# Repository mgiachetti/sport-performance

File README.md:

# Sport Performance

Plataforma de rendimiento para deportes juveniles (M13 a M19), white-label multi-tenant. Contexto de producto y dominio en [`CLAUDE.md`](CLAUDE.md); backlog en [`docs/backlog.md`](docs/backlog.md); decisiones en [`docs/adr/`](docs/adr/).

## Requisitos

- Node 24 (`.nvmrc`)
- pnpm (versión fijada en `packageManager`; con Corepack: `corepack enable`)
- Docker, para Postgres local en los tests de integración

## Comandos

| Comando | Qué hace |
|---|---|
| `pnpm install` | Instala dependencias de todo el workspace |
| `pnpm build` | Compila los paquetes y servicios (`dist/`) en orden de dependencias |
| `pnpm lint` | ESLint con reglas *type-checked*, sin warnings permitidos |
| `pnpm typecheck` | `tsc --noEmit` en cada paquete |
| `pnpm test` | Vitest en cada paquete |
| `pnpm format` / `pnpm format:check` | Prettier en todo el repo |
| `pnpm dev` | Modo watch de cada paquete |
| `pnpm docs:check` | Valida los ADRs de `docs/adr/`, su índice y los enlaces desde `CLAUDE.md` |

Todas las tareas pasan por Turborepo y se cachean. Para correr una tarea en un solo paquete: `pnpm turbo run test --filter=@sport-performance/domain`.

## CI

GitHub Actions (`.github/workflows/ci.yml`) corre en cada PR y en cada push a `main`, con jobs en paralelo: `format`, `lint`, `typecheck`, `test`, `build` y `workflows` (actionlint y shellcheck). El job `test` tiene un Postgres 16 de servicio y expone `DATABASE_URL` para los tests de integración; localmente se levanta con Docker (`postgres:16`) y se exporta la misma variable.

El job **`ci`** agrega a todos los demás y es el único check requerido en `main`: si agregás un job, sumalo a `needs` de `ci` (el job `workflows` falla si falta). Las acciones de terceros se fijan por SHA de commit.

## Estructura

```
apps/
  api/        API HTTP (Fastify + zod, Better Auth, RLS)
  worker/     Jobs en segundo plano (pg-boss)
  web/        Web del staff (React + Vite + TanStack)
  mobile/     App de jugadores y staff (Expo)
packages/
  domain/     Modelo y fórmulas puras del dominio
  contracts/  Esquemas zod, OpenAPI y cliente tipado
  ui-tokens/  Tokens de diseño y tema por club
  i18n/       Mensajes ICU y formatos es-AR
  config/     tsconfig, ESLint y Vitest compartidos
mockups/      Maqueta de referencia (no es diseño final)
assets/       Marcas por club (assets/clubs/<club>/)
firmware/     Firmware del pod (Fase 3)
docs/         Backlog y ADRs
```

Las apps son por ahora esqueletos: cada framework entra con su propio issue del backlog.

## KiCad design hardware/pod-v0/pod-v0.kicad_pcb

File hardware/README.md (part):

# Hardware

Proyectos de KiCad del pod GNSS + IMU (Fase 3). El diseño está en [`docs/hardware/pod-v0.md`](../docs/hardware/pod-v0.md) y las decisiones en el [ADR 0105](../docs/adr/0105-pod-gnss-imu-con-telemetria-en-vivo.md).

| Carpeta | Qué hay |
|---|---|
| `pod-v0/` | Proyecto de la v0 (B-909): esquemático jerárquico, placa de 6 capas con su apilado, clases de red (`pod-v0.kicad_pro`), reglas de diseño (`pod-v0.kicad_dru`); las salidas de fabricación salen de `tools/fabricacion.py` |
| `lib/` | Librería propia: símbolos, footprints y modelos 3D de los módulos (ver [`lib/README.md`](lib/README.md)) |

## Versión de KiCad

- Los archivos se crearon en el formato de KiCad 8, que abren KiCad 8, 9 y 10. Al guardarlos con una versión más nueva, se actualizan a su formato: a partir de ahí hay que usar esa versión o una posterior. **La placa (`pod-v0.kicad_pcb`) ya está en el formato de KiCad 10** desde el 14/11/2026 (contorno, tornillos y zonas guardados con el pcbnew 10.0.8 de la imagen del CI): se abre con KiCad 10 o posterior. El esquemático sigue en el de KiCad 8.
- El CI usa la imagen oficial `kicad/kicad:10.0.8`, fijada por digest en `.github/workflows/hardware.yml`. Lee los archivos de cualquiera de esas versiones.

## Cómo se trabaja

- **Ubicación y ruteo, a mano en KiCad** desde el arranque de `ubicar.py` y `rutear.py` (15/11/2026), en especial la RF: línea de 50 Ω, plano de tierra del patch GNSS (la antena principal: patch pasivo apilado L1 + L5 en la placa, con SAW y LNA montados; la Taoglas activa va por U.FL como rescate), separación de LoRa.
- **Claude Code** se encarga de:
  - generar y revisar los símbolos y footprints de los módulos a partir de las hojas;
  - correr ERC y DRC;
  - preparar las salidas de fabricación;
  - revisar cada cambio del esquemático o de la placa en el PR, contra `docs/hardware/pod-v0.md`.
- **El esquemático se genera** desde una netlist declarativa (ver abajo): siete hojas jerárquicas (`power`, `gnss_rf`, `mcu_radio`, `sensors`, `storage`, `usb_dock`, `uwb`) con todas las partes de `docs/hardware/pod-v0.md`, incluidos los lugares de rescate (marcados con el DNP nativo de KiCad). **La placa tiene todas las partes ubicadas y desde el 23/11/2026 es de 6 capas, ruteada entera por script desde el 26/11/2026** (ver "Ubicación inicial" y "Ruteo"), además del apilado de 6 capas, el contorno de 50 × 70 mm, las reglas de diseño y las zonas de las antenas (ver "Reglas de diseño de la placa").

## Ubicación inicial (`tools/ubicar.py`)

Las partes entraron a la placa el 15/11/2026 con `tools/ubicar.py`, una herramienta **de una sola vez** (bootstrap): desde ahí **la ubicación y el ruteo siguen a mano en KiCad** y la fuente es la placa, no la tabla. Corre dentro de la imagen de KiCad del CI (usa el módulo `pcbnew` y `kicad-cli`):

```sh
docker run --rm -e HOME=/tmp -v "$PWD:/work" -w /work kicad/kicad:10.0.8@sha256:3f4a… python3 hardware/tools/ubicar.py
```

1. Exporta la netlist del esquemático con `kicad-cli sch export netlist` (lo mismo que lee "Tools → Update PCB from Schematic").
2. Agrega cada footprint que falta con lo que escribe la actualización desde el esquemático: referencia, valor, los campos del símbolo (MPN, LCSC, Fabricante, Verificado, Nota), el camino de la hoja (así una actualización posterior desde KiCad y `--schematic-parity` los reconocen), DNP, si va a la BOM y la red de cada pad. Los pines sin conectar quedan en redes `unconnected-(…)`, como las crea KiCad.
3. Ubica cada parte según [`tools/datos/ubicacion_pod_v0.csv`](tools/datos/ubicacion_pod_v0.csv) (`ref`, `x`, `y` en mm del documento, origen (0; 0) = (100; 100) en KiCad; `rot` como la muestra KiCad; `cara` F o B; `fijo` = bloqueado; `nota`), pone las referencias en 0,8 mm en un lugar libre al lado de cada parte (o las oculta en la serigrafía si no hay; siguen en F.Fab/B.Fab), rellena las zonas y guarda. No rutea nada. No toca `pod-v0.kicad_pro` (guardar desde Python lo reescribe entero).

Por defecto **solo agrega y ubica las partes que faltan** (por ejemplo, después de sumar una parte en `diseno.py`) y no mueve ni retoca las que ya están: sobre la placa del repositorio no cambia nada (verificado: correrla de nuevo deja el archivo igual). `--reubicar-todo` vuelve a poner cada parte en su lugar de la tabla, bloqueadas incluidas, y no corre si la placa ya tiene pistas o vías. Todas las partes del esquemático van en la placa: la tapa blindada `SH201`, la única que había quedado afuera ("excluir de la placa"), salió del diseño el 15/11/2026 (`docs/hardware/pod-v0-ubicacion-y-carcasa.md`, sección 9). La prueba de ruteo que respalda la ubicación está en la misma sección.

## Ruteo (`tools/rutear.py`)

La placa está **ruteada entera** desde el 26/11/2026: 0 conexiones sin rutear, 0 violaciones y 0 diferencias con el esquemático. Desde el 28/11/2026 **no tiene vías en los pads**, así que no necesita relleno de resina (ADR 0105, "Registro de decisiones"). Se ruteó por script en 4 capas el 15 y 16/11/2026, en parte (quedaron 147 conexiones en 55 redes); después de tres corridas de Quilter y del router propio que no la cerraron, desde el 23/11/2026 es de **6 capas** (ADR 0105, "Registro de decisiones"), y la versión del repositorio sale de una corrida completa desde la placa ubicada (detalle en [`pod-v0-ubicacion-y-carcasa.md`](../docs/hardware/pod-v0-ubicacion-y-carcasa.md), sección 9, "Ruteo"). Como `ubicar.py`, es un procedimiento **de una sola vez**: desde ahí la fuente es la placa y los cambios siguen a mano en KiCad (las pistas de `criticas` quedan bloqueadas). **No hay que volver a correrlo sobre la placa del repositorio**: se corre en una copia (`--placa`) y la placa nueva reemplaza a la otra solo si el DRC del CI pasa entero. Cada paso corre en la imagen de KiCad del CI. Lleva unas 14 h en total, casi todo `resto`: sin vías en los pads, cada vuelta tarda unos 6 min.

```sh
K="docker run --rm -e HOME=/tmp -v $PWD:/work -w /work kicad/kicad:10.0.8@sha256:3f4a…"
P="--placa hardware/pod-v0/copia.kicad_pcb"  # una copia de la placa, con su .kicad_pro y .kicad_dru al lado
$K python3 hardware/tools/ubicar.py $P             # redes de cada pad desde el esquemático
$K python3 hardware/tools/rutear.py limpiar $P     # saca pistas, vías y planos de L1, L3, L4 y L6
$K python3 hardware/tools/rutear.py criticas $P --forzar  # pasivas de MOVES y redes críticas, bloqueadas
$K python3 hardware/tools/rutear.py abanico $P     # una vía de GND al lado de cada pad de GND
$K python3 hardware/tools/rutear.py resto $P --vueltas 128  # todo lo demás salvo GND (tools/laberinto.py)
$K python3 hardware/tools/rutear.py reparar $P --margen 0.5  # las redes sin terminar y las de al lado, otra vez
$K python3 hardware/tools/rutear.py planos $P      # relleno de GND en L1, L3, L4 y L6 y costura; rellena
$K python3 hardware/tools/rutear.py remate $P      # lo que haya quedado suelto, por el lugar libre
$K python3 hardware/tools/rutear.py podar $P       # saca lo que el DRC marca y el cobre colgado
$K python3 hardware/tools/rutear.py rescate $P     # vía para los pads de GND encerrados, si queda alguno
$K python3 hardware/tools/rutear.py podar $P
# mientras quede algo sin rutear: retocar con otro radio, y planos, remate, podar, rescate y podar
$K python3 hardware/tools/rutear.py retocar $P --radio 2.25
```

**Cómo salió la placa del repositorio (28/11/2026).** Hizo falta más que la secuencia de arriba:
- `resto` con 128 vueltas llegó a 3 redes en conflicto en la vuelta 118 y volvió a esa vuelta al final.
- `reparar --margen 0.5` dejó una sola conexión sin rutear.
- El escape de `BAT_NTC` y la vía de GND del eFuse de `pads_encerrados` se agregaron sobre esa placa con un script de una sola vez, que tiene las mismas pistas que `criticas`. Cada uno levantó y volvió a rutear las redes con las que chocaba.
- Después hubo dos pasadas de `retocar`: con 2 mm de radio quedaron 2 conexiones, y con 2,25 mm, 0.

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
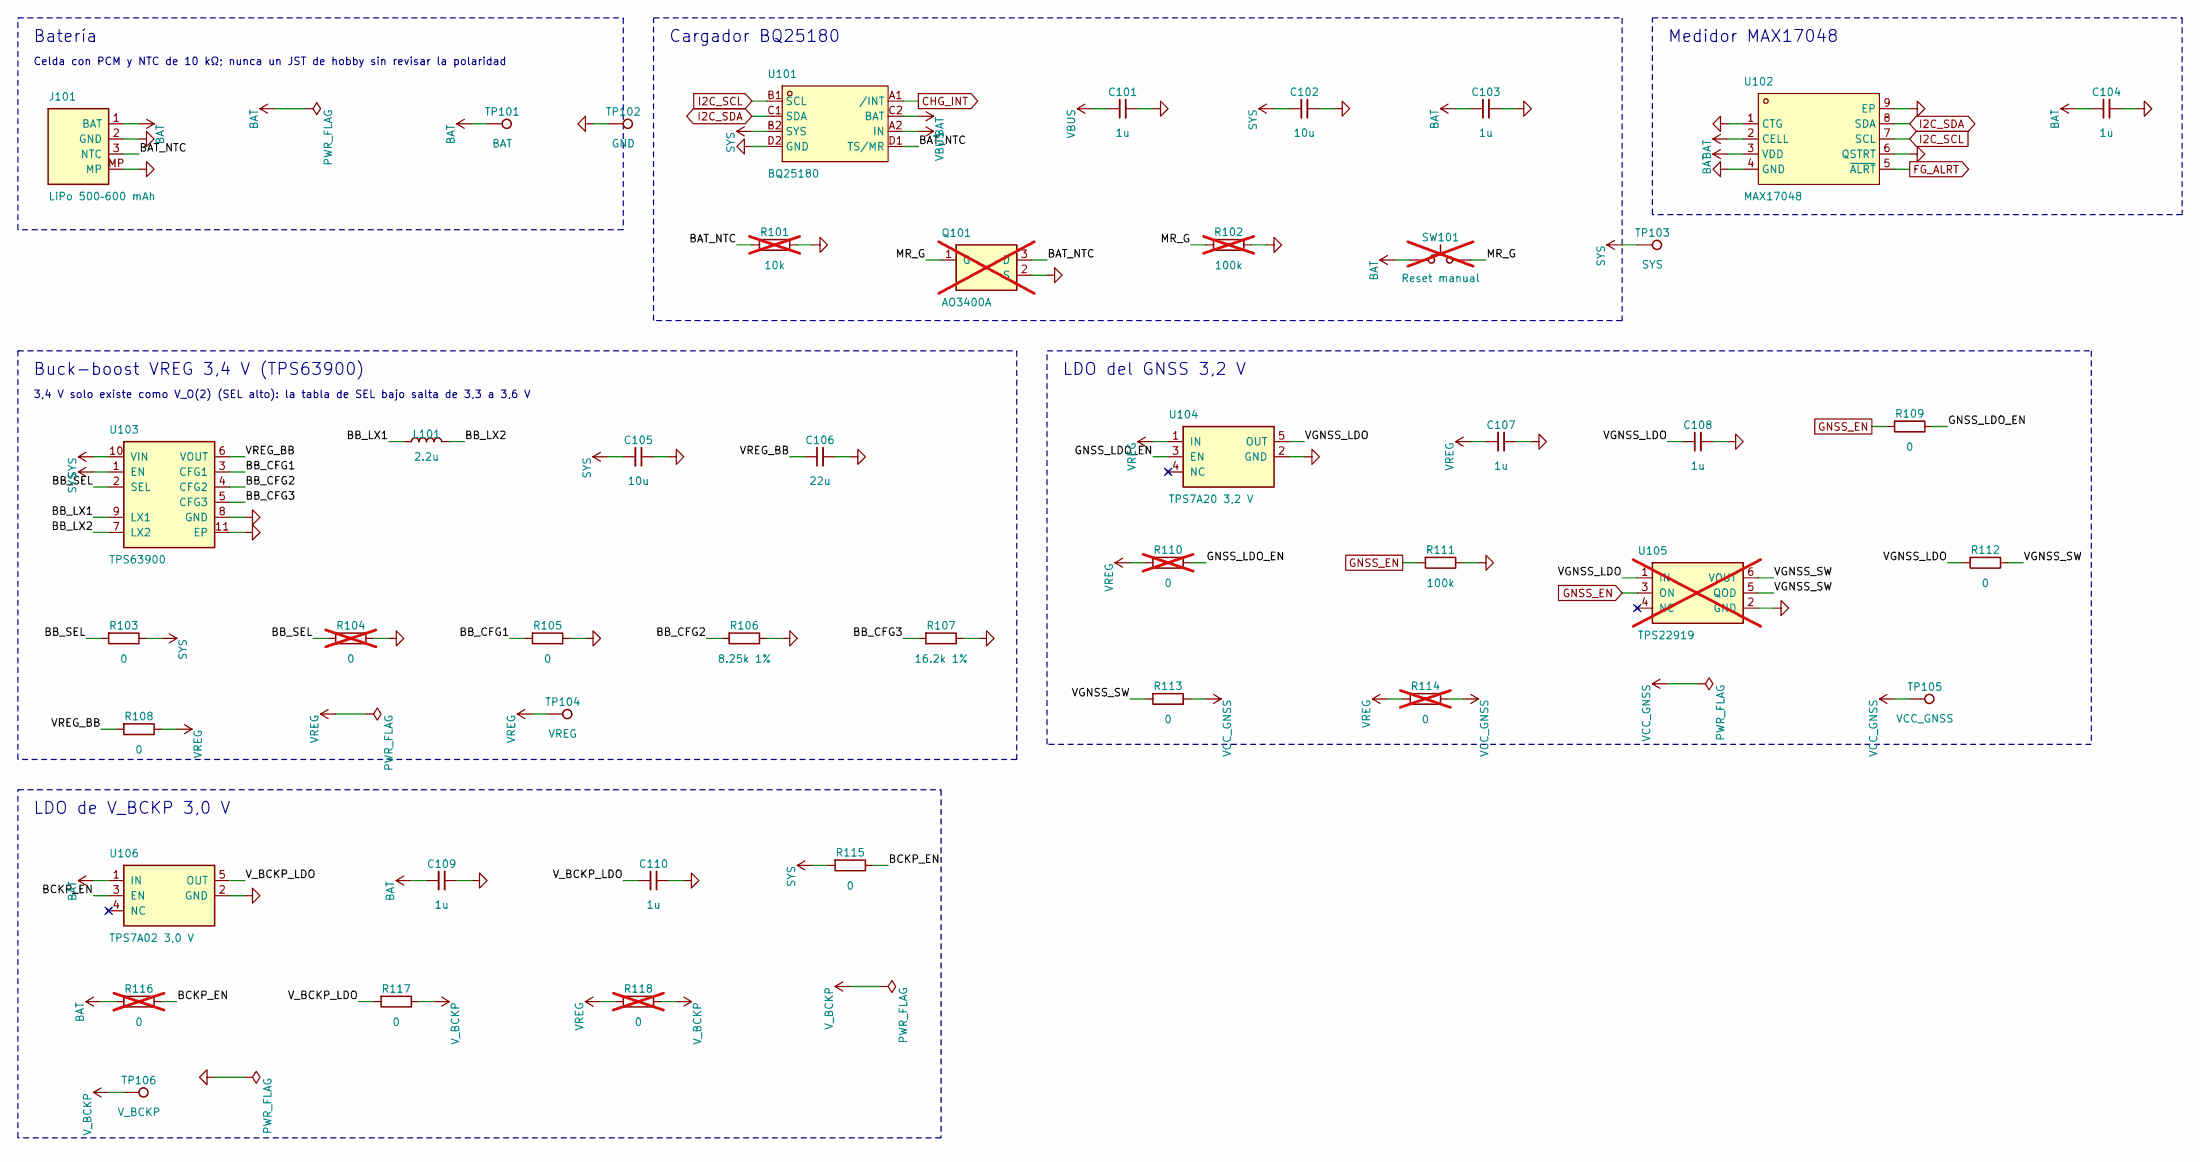
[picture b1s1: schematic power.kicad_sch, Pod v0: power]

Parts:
C101, C103, C104, C107, C108, C109, C110: 1u; C_0402_1005Metric; MPN CL05A105KA5NQNC; LCSC C52923
C102, C105: 10u; C_0603_1608Metric; MPN CL10A106KP8NNNC; LCSC C19702
C106: 22u; C_0603_1608Metric; MPN CL10A226MQ8NRNC; LCSC C59461
J101: LiPo 500–600 mAh; JST_GH_SM03B-GHS-TB_1x03-1MP_P1.25mm_Horizontal; MPN SM03B-GHS-TB(LF)(SN); LCSC C514175
L101: 2.2u; L_Murata_DFE201610P; MPN DFE201612E-2R2M=P2; LCSC C337893
Q101: AO3400A; SOT-23; MPN AO3400A; LCSC C20917; not fitted
R101: 10k; R_0402_1005Metric; MPN 0402WGF1002TCE; LCSC C25744; not fitted
R102: 100k; R_0402_1005Metric; MPN 0402WGF1003TCE; LCSC C25741; not fitted
R103, R105, R108, R109, R112, R113, R115, R117: 0; R_0402_1005Metric; MPN 0402WGF0000TCE; LCSC C17168
R104, R110, R114, R116, R118: 0; R_0402_1005Metric; MPN 0402WGF0000TCE; LCSC C17168; not fitted
R106: 8.25k 1%; R_0402_1005Metric; MPN 0402WGF8251TCE; LCSC C95598
R107: 16.2k 1%; R_0402_1005Metric; MPN 0402WGF1622TCE; LCSC C27176
R111: 100k; R_0402_1005Metric; MPN 0402WGF1003TCE; LCSC C25741
SW101: Reset manual; SW_SPST_TL3342; MPN TL3342F450QG; LCSC C2886897; not fitted
TP101: BAT; TestPoint_Pad_D1.0mm
TP102: GND; TestPoint_Pad_D1.0mm
TP103: SYS; TestPoint_Pad_D1.0mm
TP104: VREG; TestPoint_Pad_D1.0mm
TP105: VCC_GNSS; TestPoint_Pad_D1.0mm
TP106: V_BCKP; TestPoint_Pad_D1.0mm
U101: BQ25180; DSBGA-8_L1.6-W0.9-R2-C4-P0.40-BL; MPN BQ25180YBGR; LCSC C3682423
U102: MAX17048; TDFN-8_L2.0-W2.0-P0.50-BL-EP1.2; MPN MAX17048G+T10; LCSC C2682616
U103: TPS63900; Texas_DSK0010A_WSON-10-1EP_2.5x2.5mm_P0.5mm_EP1.2x2mm_Therm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; MPN TPS63900DSKR; LCSC C1518762
U104: TPS7A20 3,2 V; SOT-23-5; MPN TPS7A2032PDBVR; LCSC C2877862
U105: TPS22919; SOT-363_SC-70-6; MPN TPS22919DCKR; LCSC C2149796; not fitted
U106: TPS7A02 3,0 V; SOT-23-5; MPN TPS7A0230PDBVR; LCSC C3747031

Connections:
/power/BAT_NTC: J101.3 (NTC), Q101.3 (D), R101.1, U101.D1 (TS/MR)
/power/BB_CFG1: R105.1, U103.3 (CFG1)
/power/BB_CFG2: R106.1, U103.4 (CFG2)
/power/BB_CFG3: R107.1, U103.5 (CFG3)
/power/BB_LX1: L101.1, U103.9 (LX1)
/power/BB_LX2: L101.2, U103.7 (LX2)
/power/BB_SEL: R103.1, R104.1, U103.2 (SEL)
/power/BCKP_EN: R115.2, R116.2, U106.3 (EN)
/power/GNSS_LDO_EN: R109.2, R110.2, U104.3 (EN)
/power/MR_G: Q101.1 (G), R102.1, SW101.2
/power/VGNSS_LDO: C108.1, R112.1, U104.5 (OUT), U105.1 (IN)
/power/VGNSS_SW: R112.2, R113.1, U105.5 (QOD), U105.6 (VOUT)
/power/VREG_BB: C106.1, R108.1, U103.6 (VOUT)
/power/V_BCKP_LDO: C110.1, R117.1, U106.5 (OUT)
BAT: C103.1, C104.1, C109.1, J101.1 (BAT), R116.1, SW101.1, TP101.1, U101.C2 (BAT), U102.2 (CELL), U102.3 (VDD), U106.1 (IN)
CHG_INT: U101.A1 (/INT); also elsewhere on the board
FG_ALRT: U102.5 (~ALRT); also elsewhere on the board
GND: C101.2, C102.2, C103.2, C104.2, C105.2, C106.2, C107.2, C108.2, C109.2, C110.2, J101.2 (GND), J101.MP, Q101.2 (S), R101.2, R102.2, R104.2, R105.2, R106.2, R107.2, R111.2, TP102.1, U101.D2 (GND), U102.1 (CTG), U102.4 (GND), U102.6 (QSTRT), U102.9 (EP), U103.8 (GND), U103.11 (EP), U104.2 (GND), U105.2 (GND), U106.2 (GND); also elsewhere on the board
GNSS_EN: R109.1, R111.1, U105.3 (ON); also elsewhere on the board
I2C_SCL: U101.B1 (SCL), U102.7 (SCL); also elsewhere on the board
I2C_SDA: U101.C1 (SDA), U102.8 (SDA); also elsewhere on the board
SYS: C102.1, C105.1, R103.2, R115.1, TP103.1, U101.B2 (SYS), U103.1 (EN), U103.10 (VIN); also elsewhere on the board
VBUS: C101.1, U101.A2 (IN); also elsewhere on the board
VCC_GNSS: R113.2, R114.2, TP105.1; also elsewhere on the board
VREG: C107.1, R108.2, R110.1, R114.1, R118.1, TP104.1, U104.1 (IN); also elsewhere on the board
V_BCKP: R117.2, R118.2, TP106.1; also elsewhere on the board

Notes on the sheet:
Batería
Celda con PCM y NTC de 10 kΩ; nunca un JST de hobby sin revisar la polaridad
Cargador BQ25180
Medidor MAX17048
Buck-boost VREG 3,4 V (TPS63900)
3,4 V solo existe como V_O(2) (SEL alto): la tabla de SEL bajo salta de 3,3 a 3,6 V
LDO del GNSS 3,2 V
LDO de V_BCKP 3,0 V

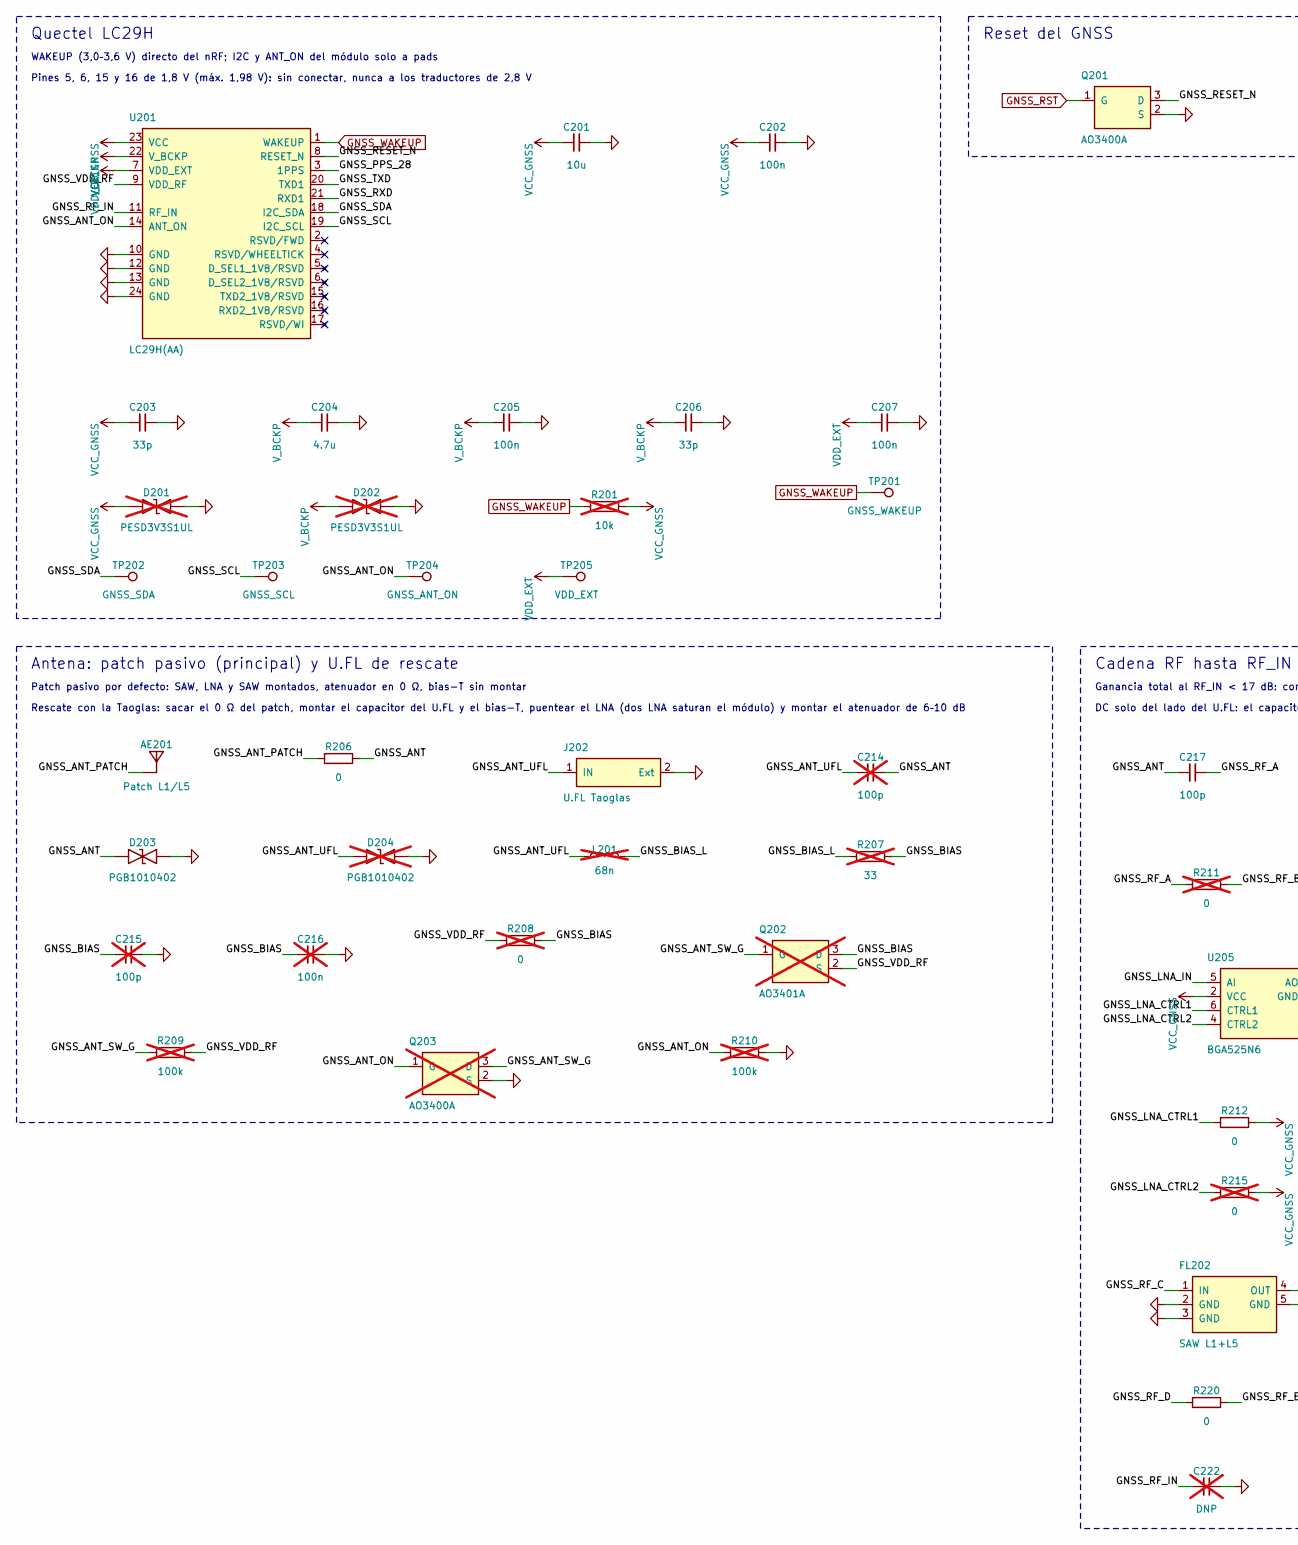
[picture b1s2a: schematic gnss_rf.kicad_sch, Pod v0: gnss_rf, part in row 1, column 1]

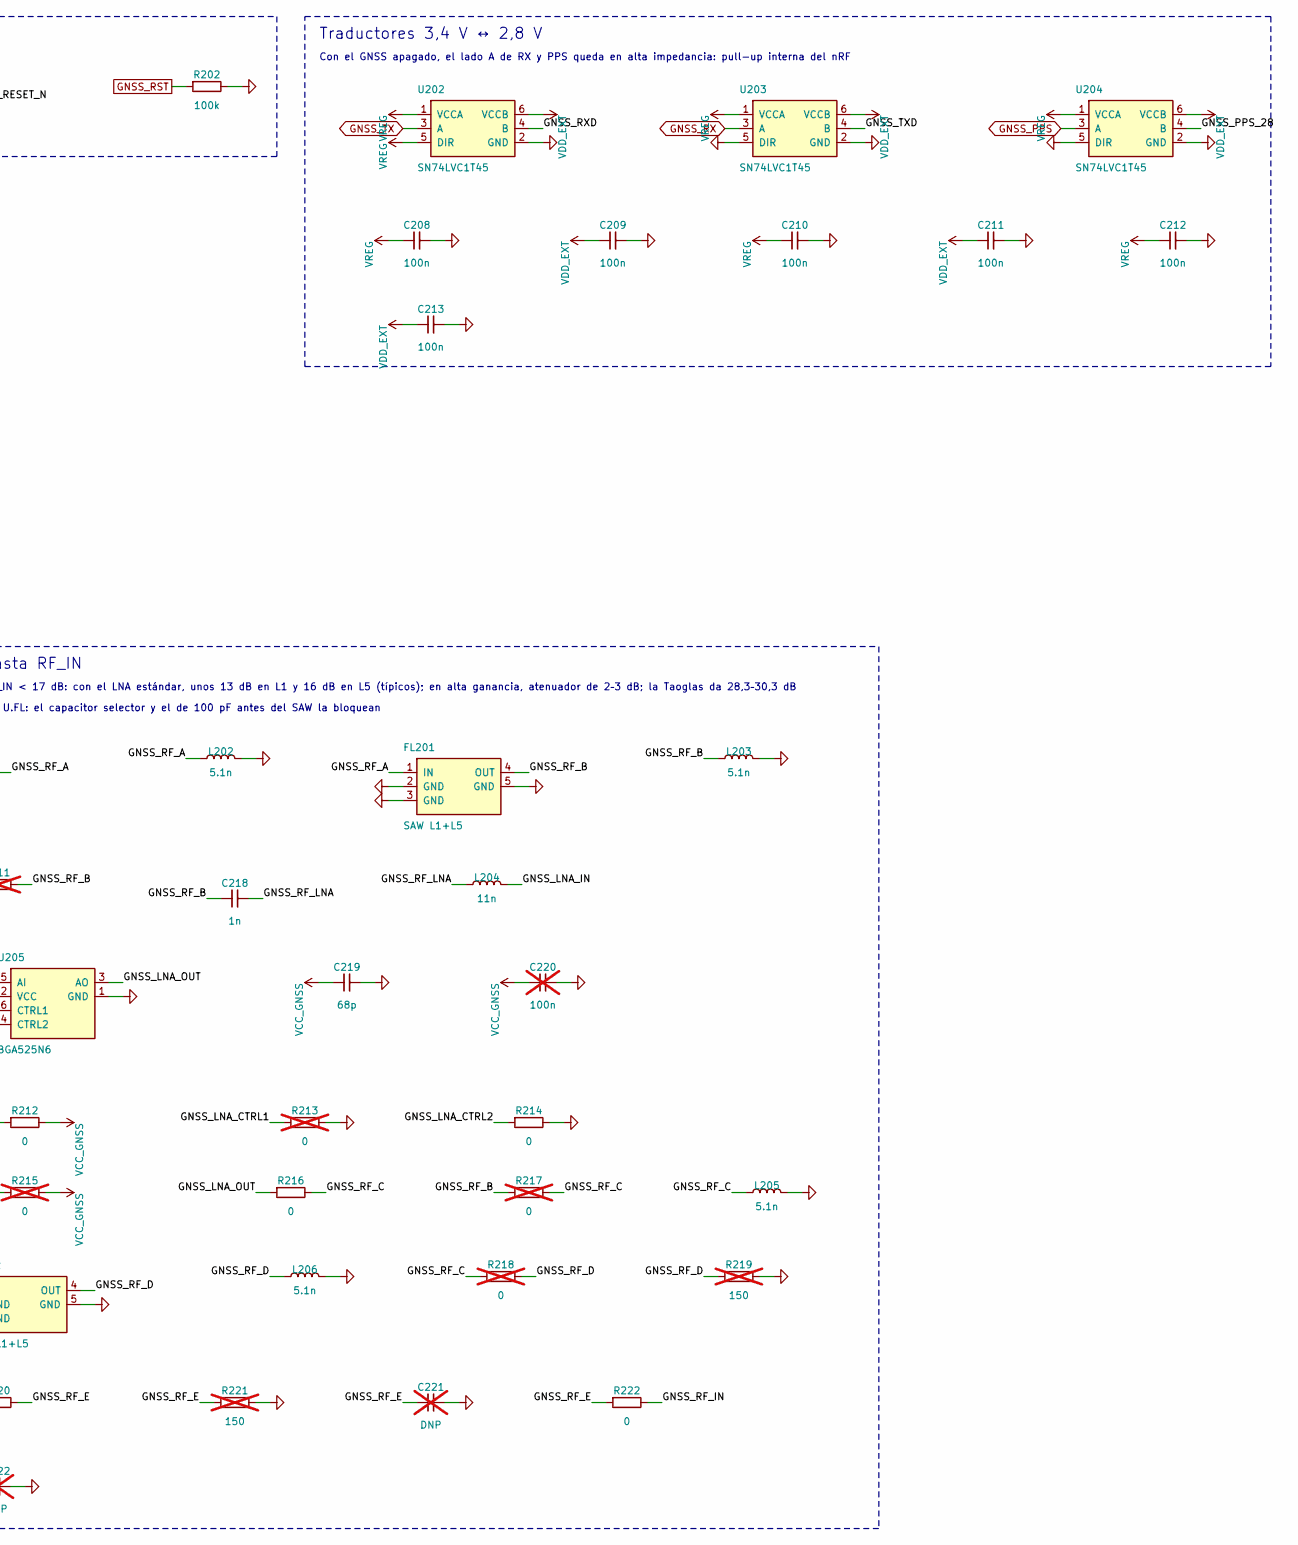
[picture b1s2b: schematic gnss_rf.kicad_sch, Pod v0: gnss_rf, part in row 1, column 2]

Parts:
AE201: Patch L1/L5; Taoglas_GVLB258.A_25x25mm; MPN GVLB258.A
C201: 10u; C_0603_1608Metric; MPN CL10A106KP8NNNC; LCSC C19702
C202, C205, C207, C208, C209, C210, C211, C212, C213: 100n; C_0402_1005Metric; MPN CL05B104KO5NNNC; LCSC C1525
C203, C206: 33p; C_0402_1005Metric; MPN CL05C330JB5NNNC; LCSC C70465
C204: 4.7u; C_0603_1608Metric; MPN CL10A475KO8NNNC; LCSC C19666
C214, C215: 100p; C_0402_1005Metric; MPN GRM1555C1H101JA01D; LCSC C77177; not fitted
C216, C220: 100n; C_0402_1005Metric; MPN CL05B104KO5NNNC; LCSC C1525; not fitted
C217: 100p; C_0402_1005Metric; MPN GRM1555C1H101JA01D; LCSC C77177
C218: 1n; C_0402_1005Metric; MPN GRM1555C1H102JA01D; LCSC C76947
C219: 68p; C_0402_1005Metric; MPN GRM1555C1H680JA01D; LCSC C76977
C221, C222: DNP; C_0402_1005Metric; not fitted
D201, D202: PESD3V3S1UL; D_SOD-882; MPN PESD3V3S1UL,315; LCSC C70371; not fitted
D203: PGB1010402; D_0402_1005Metric; MPN PGB1010402KR; LCSC C10676
D204: PGB1010402; D_0402_1005Metric; MPN PGB1010402KR; LCSC C10676; not fitted
FL201, FL202: SAW L1+L5; Qualcomm_B39162B8389P810_1.4x1.1mm; MPN B39162B8389P810; LCSC C5556161
J202: U.FL Taoglas; U.FL_Hirose_U.FL-R-SMT-1_Vertical; MPN U.FL-R-SMT-1(10); LCSC C88373
L201: 68n; L_0402_1005Metric; MPN LQW15AN68NJ00D; LCSC C98065; not fitted
L202, L203, L205, L206: 5.1n; L_0402_1005Metric; MPN LQW15AN5N1C00D; LCSC C113117
L204: 11n; L_0402_1005Metric; MPN LQW15AN11NG00D; LCSC C113109
Q201: AO3400A; SOT-23; MPN AO3400A; LCSC C20917
Q202: AO3401A; SOT-23; MPN AO3401A; LCSC C15127; not fitted
Q203: AO3400A; SOT-23; MPN AO3400A; LCSC C20917; not fitted
R201: 10k; R_0402_1005Metric; MPN 0402WGF1002TCE; LCSC C25744; not fitted
R202: 100k; R_0402_1005Metric; MPN 0402WGF1003TCE; LCSC C25741
R206, R212, R214, R216, R220, R222: 0; R_0402_1005Metric; MPN 0402WGF0000TCE; LCSC C17168
R207: 33; R_0805_2012Metric; MPN 0805W8F330JT5E; LCSC C17634; not fitted
R208, R211, R213, R215, R217, R218: 0; R_0402_1005Metric; MPN 0402WGF0000TCE; LCSC C17168; not fitted
R209, R210: 100k; R_0402_1005Metric; MPN 0402WGF1003TCE; LCSC C25741; not fitted
R219, R221: 150; R_0402_1005Metric; MPN 0402WGF1500TCE; LCSC C25082; not fitted
TP201: GNSS_WAKEUP; TestPoint_Pad_D1.0mm
TP202: GNSS_SDA; TestPoint_Pad_D1.0mm
TP203: GNSS_SCL; TestPoint_Pad_D1.0mm
TP204: GNSS_ANT_ON; TestPoint_Pad_D1.0mm
TP205: VDD_EXT; TestPoint_Pad_D1.0mm
U201: LC29H(AA); Quectel_LC29H_LCC-24_12.2x16.0mm_P1.1mm; MPN LC29HAAMD; LCSC C22403415
U202, U203, U204: SN74LVC1T45; SOT-23-6; MPN SN74LVC1T45DBVR; LCSC C7843
U205: BGA525N6; Infineon_PG-TSNP-6-10_1.1x0.7mm_P0.4mm; MPN BGA525N6E6327XTSA1; LCSC C18337445

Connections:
/gnss_rf/GNSS_ANT: C214.2, C217.1, D203.1, R206.2
/gnss_rf/GNSS_ANT_ON: Q203.1 (G), R210.1, TP204.1, U201.14 (ANT_ON)
/gnss_rf/GNSS_ANT_PATCH: AE201.1, R206.1
/gnss_rf/GNSS_ANT_SW_G: Q202.1 (G), Q203.3 (D), R209.1
/gnss_rf/GNSS_ANT_UFL: C214.1, D204.1, J202.1 (IN), L201.1
/gnss_rf/GNSS_BIAS: C215.1, C216.1, Q202.3 (D), R207.2, R208.2
/gnss_rf/GNSS_BIAS_L: L201.2, R207.1
/gnss_rf/GNSS_LNA_CTRL1: R212.1, R213.1, U205.6 (CTRL1)
/gnss_rf/GNSS_LNA_CTRL2: R214.1, R215.1, U205.4 (CTRL2)
/gnss_rf/GNSS_LNA_IN: L204.2, U205.5 (AI)
/gnss_rf/GNSS_LNA_OUT: R216.1, U205.3 (AO)
/gnss_rf/GNSS_PPS_28: U201.3 (1PPS), U204.4 (B)
/gnss_rf/GNSS_RESET_N: Q201.3 (D), U201.8 (RESET_N)
/gnss_rf/GNSS_RF_A: C217.2, FL201.1 (IN), L202.1, R211.1
/gnss_rf/GNSS_RF_B: C218.1, FL201.4 (OUT), L203.1, R211.2, R217.1
/gnss_rf/GNSS_RF_C: FL202.1 (IN), L205.1, R216.2, R217.2, R218.1
/gnss_rf/GNSS_RF_D: FL202.4 (OUT), L206.1, R218.2, R219.1, R220.1
/gnss_rf/GNSS_RF_E: C221.1, R220.2, R221.1, R222.1
/gnss_rf/GNSS_RF_IN: C222.1, R222.2, U201.11 (RF_IN)
/gnss_rf/GNSS_RF_LNA: C218.2, L204.1
/gnss_rf/GNSS_RXD: U201.21 (RXD1), U202.4 (B)
/gnss_rf/GNSS_SCL: TP203.1, U201.19 (I2C_SCL)
/gnss_rf/GNSS_SDA: TP202.1, U201.18 (I2C_SDA)
/gnss_rf/GNSS_TXD: U201.20 (TXD1), U203.4 (B)
/gnss_rf/GNSS_VDD_RF: Q202.2 (S), R208.1, R209.2, U201.9 (VDD_RF)
GND: C201.2, C202.2, C203.2, C204.2, C205.2, C206.2, C207.2, C208.2, C209.2, C210.2, C211.2, C212.2, C213.2, C215.2, C216.2, C219.2, C220.2, C221.2, C222.2, D201.2, D202.2, D203.2, D204.2, FL201.2 (GND), FL201.3 (GND), FL201.5 (GND), FL202.2 (GND), FL202.3 (GND), FL202.5 (GND), J202.2 (Ext), L202.2, L203.2, L205.2, L206.2, Q201.2 (S), Q203.2 (S), R202.2, R210.2, R213.2, R214.2, R219.2, R221.2, U201.10 (GND), U201.12 (GND), U201.13 (GND), U201.24 (GND), U202.2 (GND), U203.2 (GND), U203.5 (DIR), U204.2 (GND), U204.5 (DIR), U205.1 (GND); also elsewhere on the board
GNSS_PPS: U204.3 (A); also elsewhere on the board
GNSS_RST: Q201.1 (G), R202.1; also elsewhere on the board
GNSS_RX: U203.3 (A); also elsewhere on the board
GNSS_TX: U202.3 (A); also elsewhere on the board
GNSS_WAKEUP: R201.1, TP201.1, U201.1 (WAKEUP); also elsewhere on the board
VCC_GNSS: C201.1, C202.1, C203.1, C219.1, C220.1, D201.1, R201.2, R212.2, R215.2, U201.23 (VCC), U205.2 (VCC); also elsewhere on the board
VDD_EXT: C207.1, C209.1, C211.1, C213.1, TP205.1, U201.7 (VDD_EXT), U202.6 (VCCB), U203.6 (VCCB), U204.6 (VCCB)
VREG: C208.1, C210.1, C212.1, U202.1 (VCCA), U202.5 (DIR), U203.1 (VCCA), U204.1 (VCCA); also elsewhere on the board
V_BCKP: C204.1, C205.1, C206.1, D202.1, U201.22 (V_BCKP); also elsewhere on the board

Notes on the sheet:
Quectel LC29H
WAKEUP (3,0–3,6 V) directo del nRF; I2C y ANT_ON del módulo solo a pads
Pines 5, 6, 15 y 16 de 1,8 V (máx. 1,98 V): sin conectar, nunca a los traductores de 2,8 V
Reset del GNSS
Traductores 3,4 V ↔ 2,8 V
Con el GNSS apagado, el lado A de RX y PPS queda en alta impedancia: pull-up interna del nRF
Antena: patch pasivo (principal) y U.FL de rescate
Patch pasivo por defecto: SAW, LNA y SAW montados, atenuador en 0 Ω, bias-T sin montar
Rescate con la Taoglas: sacar el 0 Ω del patch, montar el capacitor del U.FL y el bias-T, puentear el LNA (dos LNA saturan el módulo) y montar el atenuador de 6–10 dB
Cadena RF hasta RF_IN
Ganancia total al RF_IN < 17 dB: con el LNA estándar, unos 13 dB en L1 y 16 dB en L5 (típicos); en alta ganancia, atenuador de 2–3 dB; la Taoglas da 28,3–30,3 dB
DC solo del lado del U.FL: el capacitor selector y el de 100 pF antes del SAW la bloquean
